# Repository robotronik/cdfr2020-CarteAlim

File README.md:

# Carte alimentation du robot 2020

- [Carte alimentation du robot 2020](#carte-alimentation-du-robot-2020)
  - [Changelog](#changelog)
    - [Commits](#commits)
    - [Versions du projet](#versions-du-projet)
  - [Protection de la batterie](#protection-de-la-batterie)
    - [Protection contre la décharge](#protection-contre-la-décharge)
    - [Protection contre une inversion de la polarité](#protection-contre-une-inversion-de-la-polarité)
  - [Les sorties](#les-sorties)
    - [Partie commande](#partie-commande)
    - [Partie actionneurs](#partie-actionneurs)
    - [Table des fusibles](#table-des-fusibles)
  - [Taille des pistes](#taille-des-pistes)

## Changelog
### Commits
|Date|Nom du commit|Version du projet|
|---|---|---|
| 26/10/2020 | Fin du schema et routage
| 26/10/2020 | Changement pour ajouter la possibiliter de court circuiter les 2 buzzers ou 1|v1
| 27/10/2020 | Readme propre | Ajout du README
| 27/10/2020 | Sans regul moteurs et fix du reste |v2 bis 
| 10/11/2020 | Avec regul moteurs et texte sur autre couche | v2 (avec plan de masse)

### Versions du projet
|Version|Description|
|---|---|
|v1| Le routage est fait avec 0.5mm partout, pas de plan de masse, mauvaise empreinte pour le transistor, mauvais noms de sorties (n'indiquent pas clairement la tension)|
|v2 *| Largeur de piste tenant compte de l'intensité pouvant passer, bonne empreinte du transistor, bons noms de sortie
|v2 bis| Sorties moteurs dérégulées : elles sont "directement" reliées à la batterie|

## Protection de la batterie

### Protection contre la décharge

*Repose sur le modèle présenté dans cette vidéo : www.youtube.com/watch?v=1Fs4SfVSsLk*\
Un bipper de batterie est relié à la carte.\
Ses buzzers sont remplacés par un relais qui coupe la partie négative de la batterie (celle-ci ne peut donc plus se décharger).\
Attention le relais prévu a une alimentation de 5V max, il y a donc possibilité de mettre un pont diviseur de tension ou une diode (si cela suffit) pour réduire la tension aux bornes de Coil2 (celle issu\

><u>__/!\\__</u> Lors du branchement de la batterie, le bipper "bip" usuellement, ici ça se traduit par une coupure du relais. Il faut réactiver l'utilisation de la batterie.<br>
>**Pour réactiver l'utilisation de la batterie** : 
>- S'assurer qu'elle est chargée à un niveau suffisant
>- Appuyer sur le bouton SW1 (reset du relais)

### Protection contre une inversion de la polarité

On a un PMOS en reverse polarity protection.\
Fait-il office de protection contre les surcharges ? (à la place d'un fusible)

## Les sorties

### Partie commande

*Celle-ci est liée au SW_Starter qui est l'emplacement où devra être installée la tirette de démarrage.*

### Partie actionneurs

*Puisque le bouton d'arrêt d'urgence doit arrêter tout mouvement du robot, celui-ci n'est relié qu'à la partie actionneurs.*

### Table des fusibles
|Sortie         |Fusible (valeur estimée approximativement)|
|---            |---|
|Cmd-5V         | 1A  |
|Cmd-7V5        | 1A  |
|Motor1-12V     | 2A  |
|Motor1-12V     | 2A  |
|Actuator-5V    | 2A  |

## Taille des pistes
*https://www.digikey.com/en/resources/conversion-calculators/conversion-calculator-pcb-trace-width*

*https://www.mclpcb.com/pcb-trace-width-vs-current-table/*

|Zone           |Courant max /A|Taille estimée /mm|
|---            |---|---|
|Cmd-5V         |1 | 0.25
|Cmd-7V5        |1 | 0.25
|Motor1-18V     |2 | 0.76
|Motor2-18V     |2 | 0.76
|Actuator-5V    |2 | 0.76
|All active |6 | 3.81
|BatteryIn-18V  |8 | 5.59

$$
I_{max-battery}= \sum{I_{max-Zone-i}}
$$

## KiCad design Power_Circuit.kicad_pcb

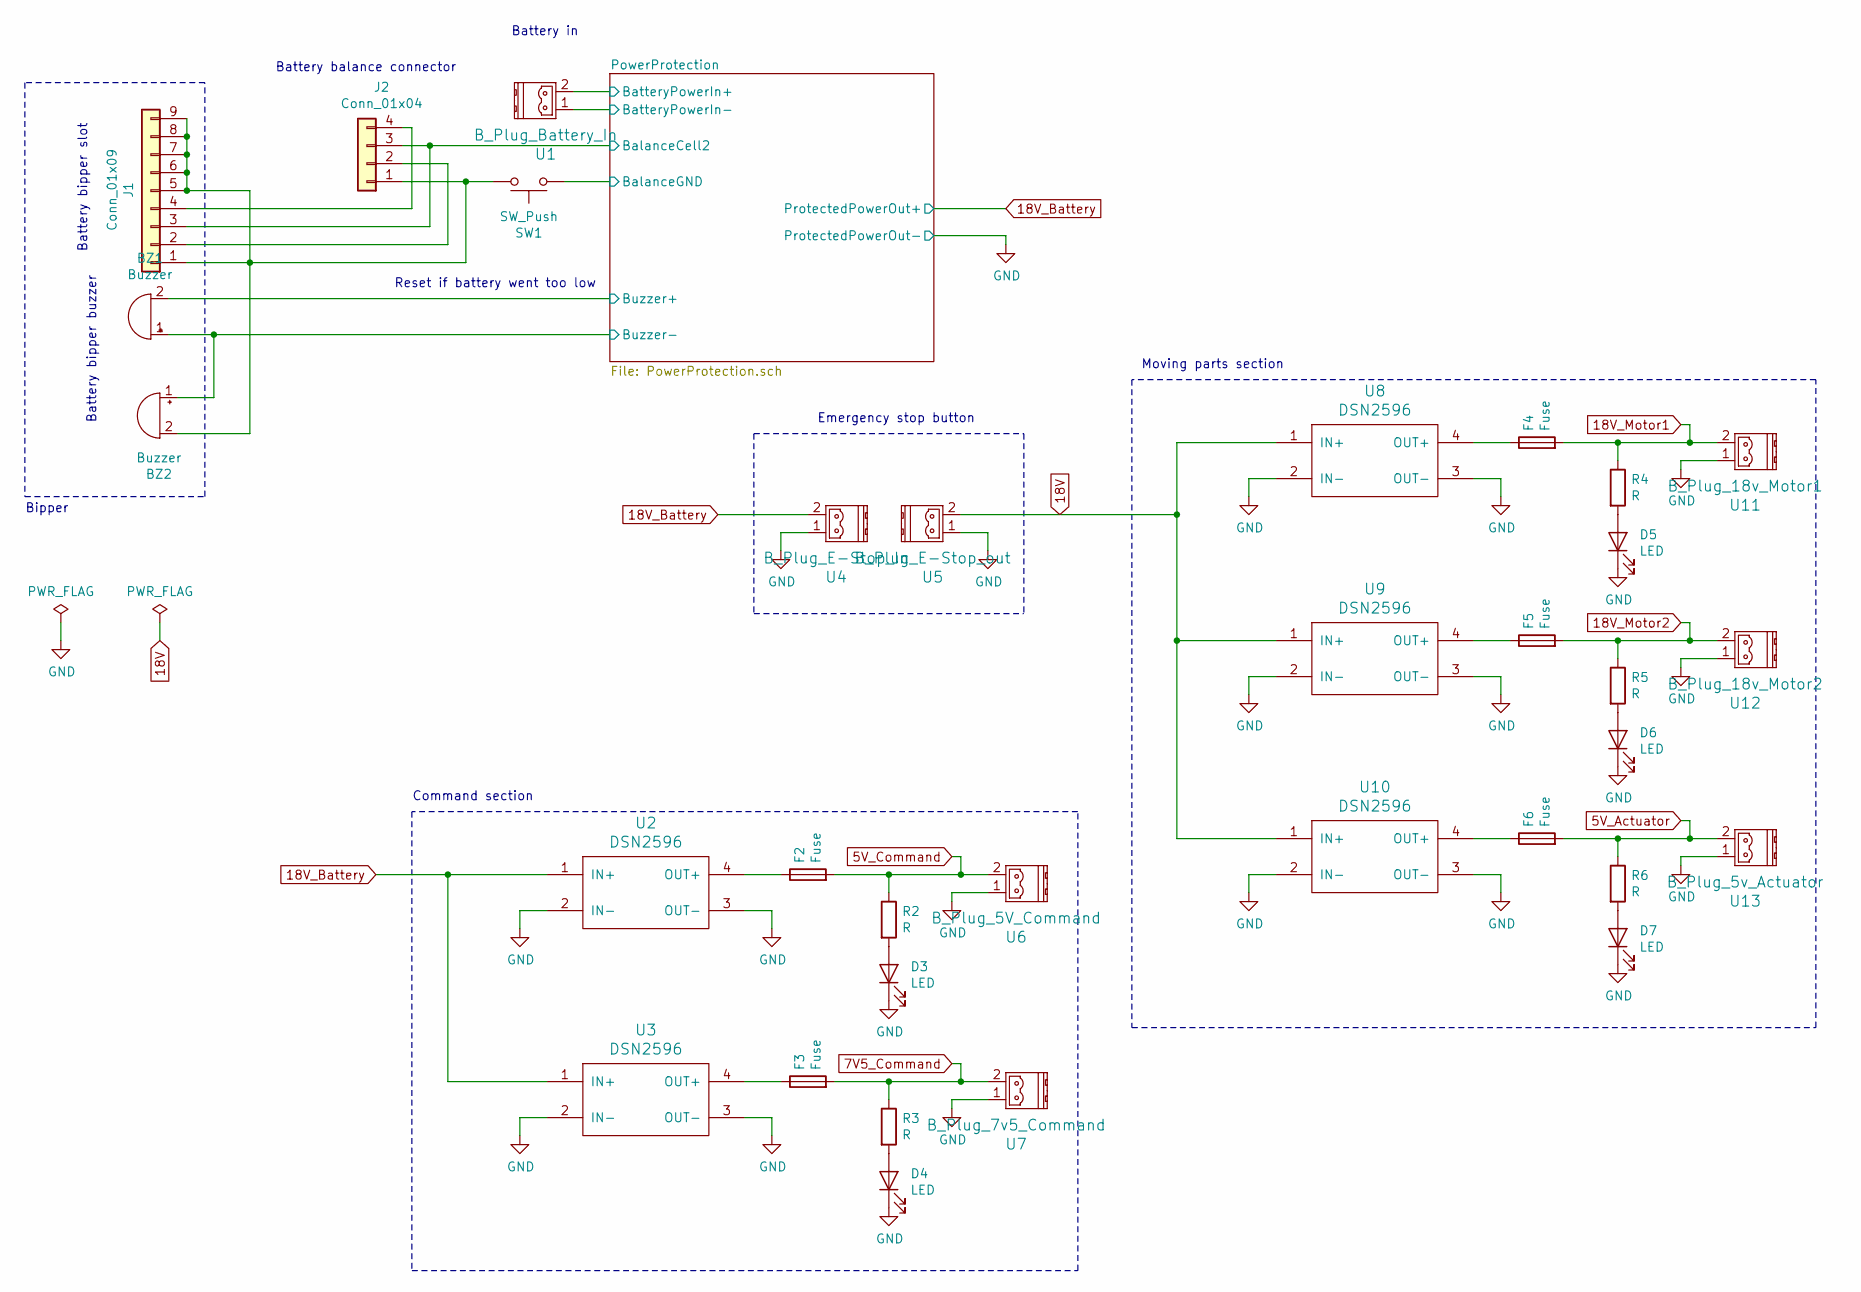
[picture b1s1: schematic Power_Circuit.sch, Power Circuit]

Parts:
BZ1, BZ2: Buzzer; Buzzer_12x9.5RM7.6
D3, D4, D5, D6, D7: LED; LED_1206_3216Metric_Pad1.42x1.75mm_HandSolder
F2, F3, F4, F5, F6: Fuse; Fuse_1210_3225Metric_Pad1.42x2.65mm_HandSolder
J1: Conn_01x09; PinSocket_1x09_P2.54mm_Horizontal
J2: Conn_01x04; PinHeader_1x04_P2.54mm_Vertical
R2, R3, R4, R5, R6: R; R_1206_3216Metric_Pad1.42x1.75mm_HandSolder
SW1: SW_Push; R_Axial_DIN0207_L6.3mm_D2.5mm_P10.16mm_Horizontal
U1: B_Plug_Battery_In; PhoenixContact_MCV_1,5_2-G-3.81_1x02_P3.81mm_Vertical
U2, U3, U8, U9, U10: DSN2596; DC_DC_LM2596_small
U4: B_Plug_E-Stop_In; PhoenixContact_MCV_1,5_2-G-3.81_1x02_P3.81mm_Vertical
U5: B_Plug_E-Stop_out; PhoenixContact_MCV_1,5_2-G-3.81_1x02_P3.81mm_Vertical
U6: B_Plug_5V_Command; PhoenixContact_MCV_1,5_2-G-3.81_1x02_P3.81mm_Vertical
U7: B_Plug_7v5_Command; PhoenixContact_MCV_1,5_2-G-3.81_1x02_P3.81mm_Vertical
U11: B_Plug_18v_Motor1; PhoenixContact_MCV_1,5_2-G-3.81_1x02_P3.81mm_Vertical
U12: B_Plug_18v_Motor2; PhoenixContact_MCV_1,5_2-G-3.81_1x02_P3.81mm_Vertical
U13: B_Plug_5v_Actuator; PhoenixContact_MCV_1,5_2-G-3.81_1x02_P3.81mm_Vertical

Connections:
5V_Actuator: F6.2, R6.1, U13.2
5V_Command: F2.2, R2.1, U6.2
7V5_Command: F3.2, R3.1, U7.2
18V: U5.2, U8.1 (IN+), U9.1 (IN+), U10.1 (IN+)
18V_Battery: U2.1 (IN+), U3.1 (IN+), U4.2; also elsewhere on the board
18V_Motor1: F4.2, R4.1, U11.2
18V_Motor2: F5.2, R5.1, U12.2
/PowerProtection/BalanceCell2: J1.3, J2.3; also elsewhere on the board
/PowerProtection/BalanceGND: SW1.1; also elsewhere on the board
/PowerProtection/BatteryPowerIn+: U1.2; also elsewhere on the board
/PowerProtection/BatteryPowerIn-: U1.1; also elsewhere on the board
/PowerProtection/Buzzer+: BZ1.2 (+); also elsewhere on the board
/PowerProtection/Buzzer-: BZ1.1 (-), BZ2.1 (-); also elsewhere on the board
GND: D3.1 (K), D4.1 (K), D5.1 (K), D6.1 (K), D7.1 (K), U2.2 (IN-), U2.3 (OUT-), U3.2 (IN-), U3.3 (OUT-), U4.1, U5.1, U6.1, U7.1, U8.2 (IN-), U8.3 (OUT-), U9.2 (IN-), U9.3 (OUT-), U10.2 (IN-), U10.3 (OUT-), U11.1, U12.1, U13.1; also elsewhere on the board
unnamed: BZ2.2 (+), J1.1, J1.5, J1.6, J1.7, J1.8, J1.9, J2.1, SW1.2
unnamed: D3.2 (A), R2.2
unnamed: D4.2 (A), R3.2
unnamed: D5.2 (A), R4.2
unnamed: D6.2 (A), R5.2
unnamed: D7.2 (A), R6.2
unnamed: F2.1, U2.4 (OUT+)
unnamed: F3.1, U3.4 (OUT+)
unnamed: F4.1, U8.4 (OUT+)
unnamed: F5.1, U9.4 (OUT+)
unnamed: F6.1, U10.4 (OUT+)
unnamed: J1.2, J2.2
unnamed: J1.4, J2.4

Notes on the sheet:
Battery in
Moving parts section
Command section
Emergency stop button
Battery bipper slot
Battery balance connector
Battery bipper buzzer
Reset if battery went too low
Bipper

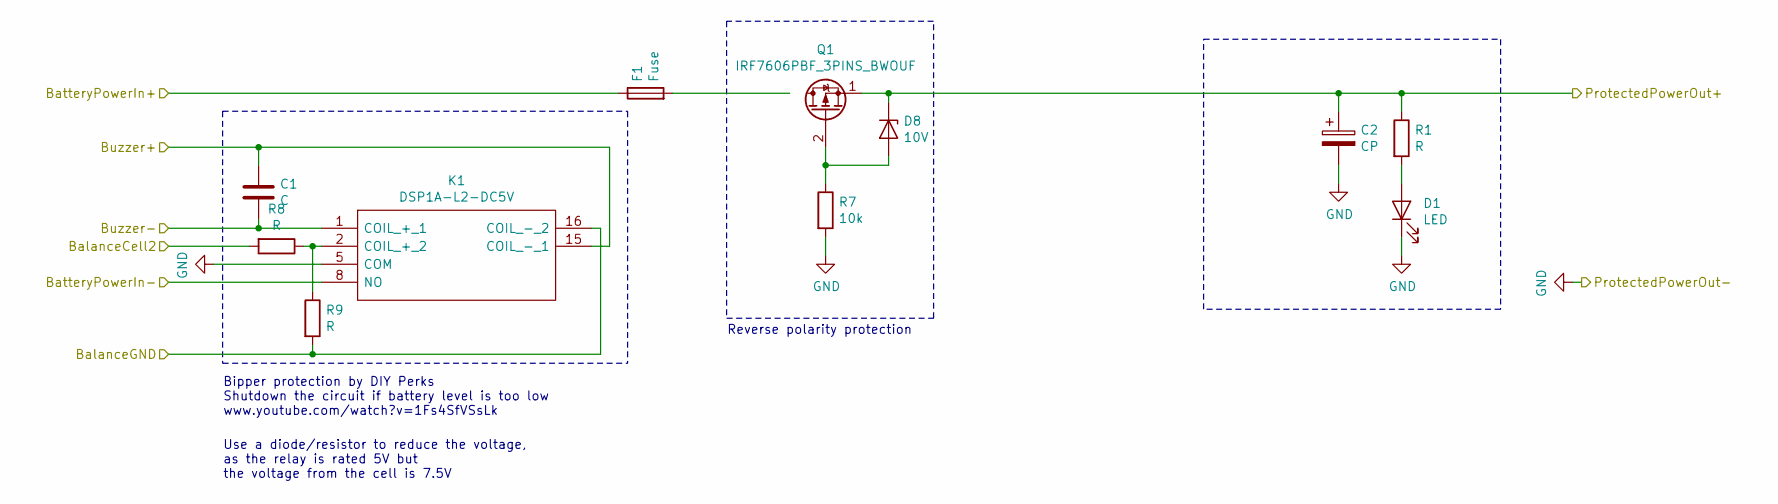
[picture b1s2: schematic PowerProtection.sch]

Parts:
C1: C; C_1206_3216Metric_Pad1.42x1.75mm_HandSolder
C2: CP; C_1206_3216Metric_Pad1.42x1.75mm_HandSolder
D1: LED; LED_1206_3216Metric_Pad1.42x1.75mm_HandSolder
D8: 10V; LED_1206_3216Metric_Pad1.42x1.75mm_HandSolder
F1: Fuse; Fuse_1210_3225Metric_Pad1.42x2.65mm_HandSolder
K1: DSP1A-L2-DC5V; DSP1AL2DC5V; Mouser Part Number 769-DSP1A-L2-DC5V
Q1: IRF7606PBF_3PINS_BWOUF; TO-252-3_TabPin2
R1, R8, R9: R; R_1206_3216Metric_Pad1.42x1.75mm_HandSolder
R7: 10k; R_1206_3216Metric_Pad1.42x1.75mm_HandSolder

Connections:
18V_Battery: C2.1, D8.1 (K), Q1.1 (S), R1.1; also elsewhere on the board
/PowerProtection/BalanceCell2: R8.2; also elsewhere on the board
/PowerProtection/BalanceGND: K1.16 (COIL_-_2), R9.2; also elsewhere on the board
/PowerProtection/BatteryPowerIn+: F1.1; also elsewhere on the board
/PowerProtection/BatteryPowerIn-: K1.8 (NO); also elsewhere on the board
/PowerProtection/Buzzer+: C1.1, K1.15 (COIL_-_1); also elsewhere on the board
/PowerProtection/Buzzer-: C1.2, K1.1 (COIL_+_1); also elsewhere on the board
GND: C2.2, D1.1 (K), K1.5 (COM), R7.2; also elsewhere on the board
unnamed: D1.2 (A), R1.2
unnamed: D8.2 (A), Q1.2 (G), R7.1
unnamed: F1.2, Q1.3 (D)
unnamed: K1.2 (COIL_+_2), R8.1, R9.1

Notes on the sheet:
Bipper protection by DIY Perks Shutdown the circuit if battery level is too low www.youtube.com/watch?v=1Fs4SfVSsLk
Reverse polarity protection
Use a diode/resistor to reduce the voltage, as the relay is rated 5V but the voltage from the cell is 7.5V

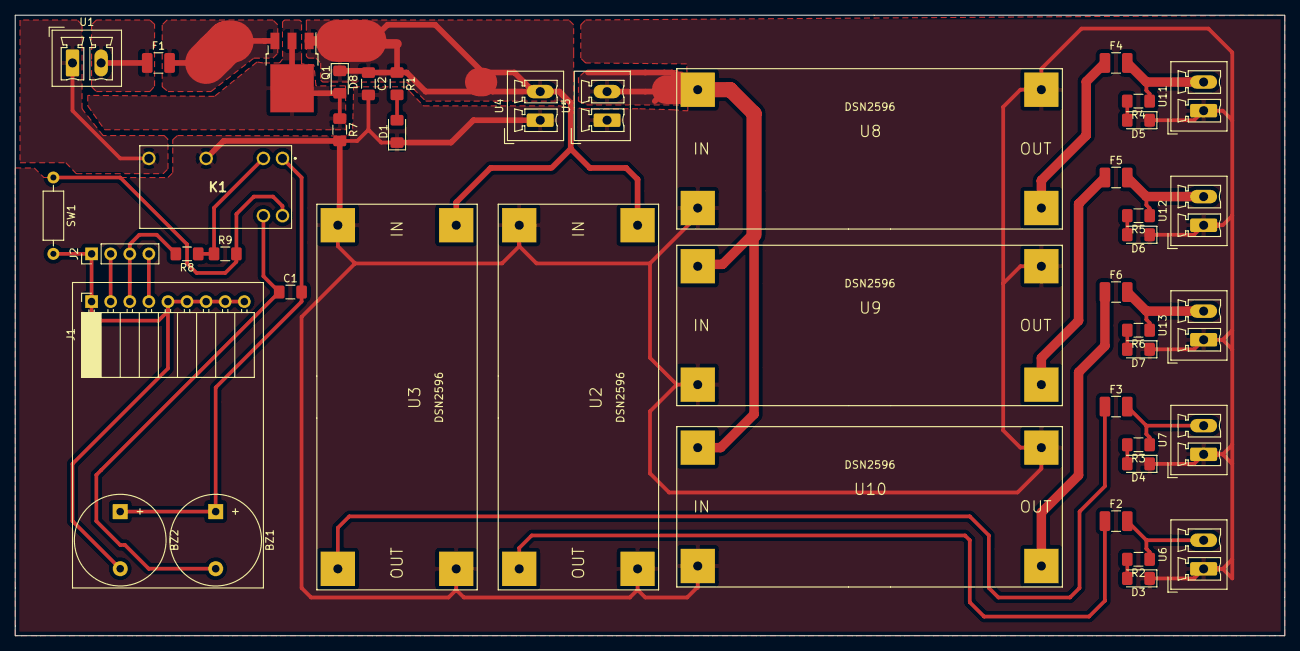
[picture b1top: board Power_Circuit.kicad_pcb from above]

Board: 2 copper layers, 168.9 x 82.6 mm, 44 parts (0 on the bottom side), 31 nets.

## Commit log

2020-09-05 Create readme1
2020-09-05 Schema sans protection batterie
2020-09-06 Ajout du schéma
    Sans protection réelle de la batterie
2020-10-15 Nouvelle avancee, manque la protection reverse polarity
2020-10-15 Il reste a trouver empreintes et router
2020-10-15 ajout de la tirette
2020-10-26 Fin du schema et routage
2020-10-26 Changement pour ajouter la possibiliter de court circuiter les 2 buzzers ou 1
2020-10-27 Readme propre
2020-10-27 Sans regul moteurs et fix du reste
2020-11-09 Avec regul moteur et texte sur autre couche
2020-11-09 update du readme
2021-01-14 Ajout BOM, suppression tirette, correction silk, correction des plans pour meilleur refroidissement du transistor notamment
2021-01-14 Changement de la liste a acheter, jaune = important et probablement pas au local
2021-01-14 apres fermeture il restait ce fichier
